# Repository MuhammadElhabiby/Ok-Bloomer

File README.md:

# Ok Bloomer

# How to Docker Windows
1. Docker Desktop runterladen und installieren https://docs.docker.com/desktop/install/windows-install/
2. WSL installieren
    1. Powershell als Admin ausführen
    2. wsl --install ausführen
    3. https://wslstorestorage.blob.core.windows.net/wslblob/wsl_update_x64.msi runterladen und installieren oder über Windows-Update installieren
4. PC neustarten
5. Docker Desktop starten und warten bis Docker Engine gestartet ist (unten links zu sehen, siehe Screenshot)

6. Konsole im repo öffnen
7. docker compose up --build ausführen
8. Nun werden die Docker Container gebaut und ausgeführt. Nach Änderungen muss der Befehl docker compose up --build erneut ausgeführt werden, um die Änderungen zu übernehmen

Die Docker Instanz kann ebenfalls über Docker Desktop verwaltet werden.

Ports:
- 127.0.0.1:7000 - Dashboard
- 127.0.0.1:7001 - MongoDB
- 127.0.0.1:7002 - MongoDB Admin Panel
- 127.0.0.1:7003 - MQTT Broker

MQTT Debug GUI Tool - https://github.com/thomasnordquist/MQTT-Explorer
https://github.com/thomasnordquist/MQTT-Explorer/releases/tag/v0.3.5

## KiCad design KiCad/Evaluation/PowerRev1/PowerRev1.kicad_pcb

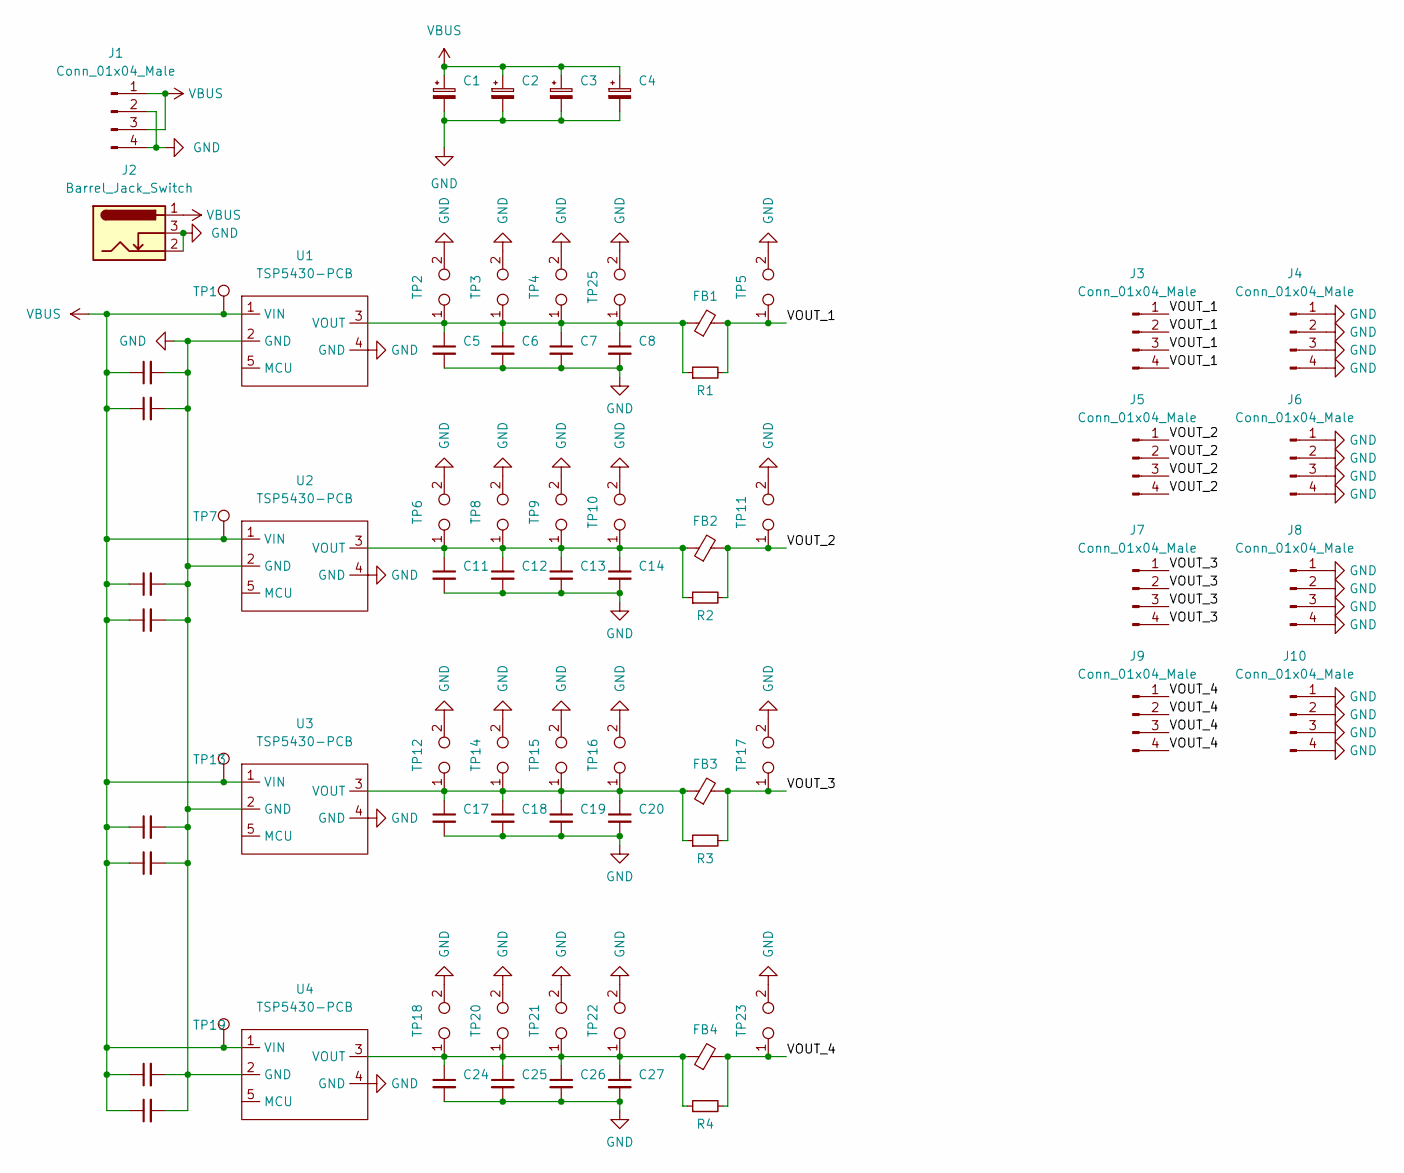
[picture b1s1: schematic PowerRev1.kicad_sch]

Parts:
C1, C2, C3, C4: C_Polarized_Small; CP_Radial_D8.0mm_P3.50mm
C5, C6, C7, C8, C9, C10, C11, C12, C13, C14, C15, C16, C17, C18, C19, C20, C21, C22, C23, C24, C25, C26, C27, C28: C_Small; 0805-1206Capacitor
FB1, FB2, FB3, FB4: FerriteBead_Small; 0805-1206Capacitor
J1, J3, J4, J5, J6, J7, J8, J9, J10: Conn_01x04_Male; PinSocket_1x04_P2.54mm_Vertical
J2: Barrel_Jack_Switch; BarrelJack_GCT_DCJ200-10-A_Horizontal
R1, R2, R3, R4: R_Small; 0805-1206Capacitor
TP1, TP7, TP13, TP19: TestPoint; TestPoint_Pad_D2.0mm
TP2, TP3, TP4, TP5, TP6, TP8, TP9, TP10, TP11, TP12, TP14, TP15, TP16, TP17, TP18, TP20, TP21, TP22, TP23, TP25: TestPoint_2Pole; TestPoint_2Pads_Pitch5.08mm_Drill1.3mm
U1, U2, U3, U4: TSP5430-PCB; TPS5430-REV3

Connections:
/VOUT_1: FB1.2, J3.1, J3.2, J3.3, J3.4, R1.2, TP5.1
/VOUT_2: FB2.2, J5.1, J5.2, J5.3, J5.4, R2.2, TP11.1
/VOUT_3: FB3.2, J7.1, J7.2, J7.3, J7.4, R3.2, TP17.1
/VOUT_4: FB4.2, J9.1, J9.2, J9.3, J9.4, R4.2, TP23.1
GND: C1.2, C2.2, C3.2, C4.2, C5.2, C6.2, C7.2, C8.2, C9.2, C10.2, C11.2, C12.2, C13.2, C14.2, C15.2, C16.2, C17.2, C18.2, C19.2, C20.2, C21.2, C22.2, C23.2, C24.2, C25.2, C26.2, C27.2, C28.2, J1.2, J1.4, J2.2, J2.3, J4.1, J4.2, J4.3, J4.4, J6.1, J6.2, J6.3, J6.4, J8.1, J8.2, J8.3, J8.4, J10.1, J10.2, J10.3, J10.4, TP2.2, TP3.2, TP4.2, TP5.2, TP6.2, TP8.2, TP9.2, TP10.2, TP11.2, TP12.2, TP14.2, TP15.2, TP16.2, TP17.2, TP18.2, TP20.2, TP21.2, TP22.2, TP23.2, TP25.2, U1.2 (GND), U1.4 (GND), U2.2 (GND), U2.4 (GND), U3.2 (GND), U3.4 (GND), U4.2 (GND), U4.4 (GND)
unnamed: C5.1, C6.1, C7.1, C8.1, FB1.1, R1.1, TP2.1, TP3.1, TP4.1, TP25.1, U1.3 (VOUT)
unnamed: C11.1, C12.1, C13.1, C14.1, FB2.1, R2.1, TP6.1, TP8.1, TP9.1, TP10.1, U2.3 (VOUT)
unnamed: C17.1, C18.1, C19.1, C20.1, FB3.1, R3.1, TP12.1, TP14.1, TP15.1, TP16.1, U3.3 (VOUT)
unnamed: C24.1, C25.1, C26.1, C27.1, FB4.1, R4.1, TP18.1, TP20.1, TP21.1, TP22.1, U4.3 (VOUT)
VBUS: C1.1, C2.1, C3.1, C4.1, C9.1, C10.1, C15.1, C16.1, C21.1, C22.1, C23.1, C28.1, J1.1, J1.3, J2.1, TP1.1, TP7.1, TP13.1, TP19.1, U1.1 (VIN), U2.1 (VIN), U3.1 (VIN), U4.1 (VIN)

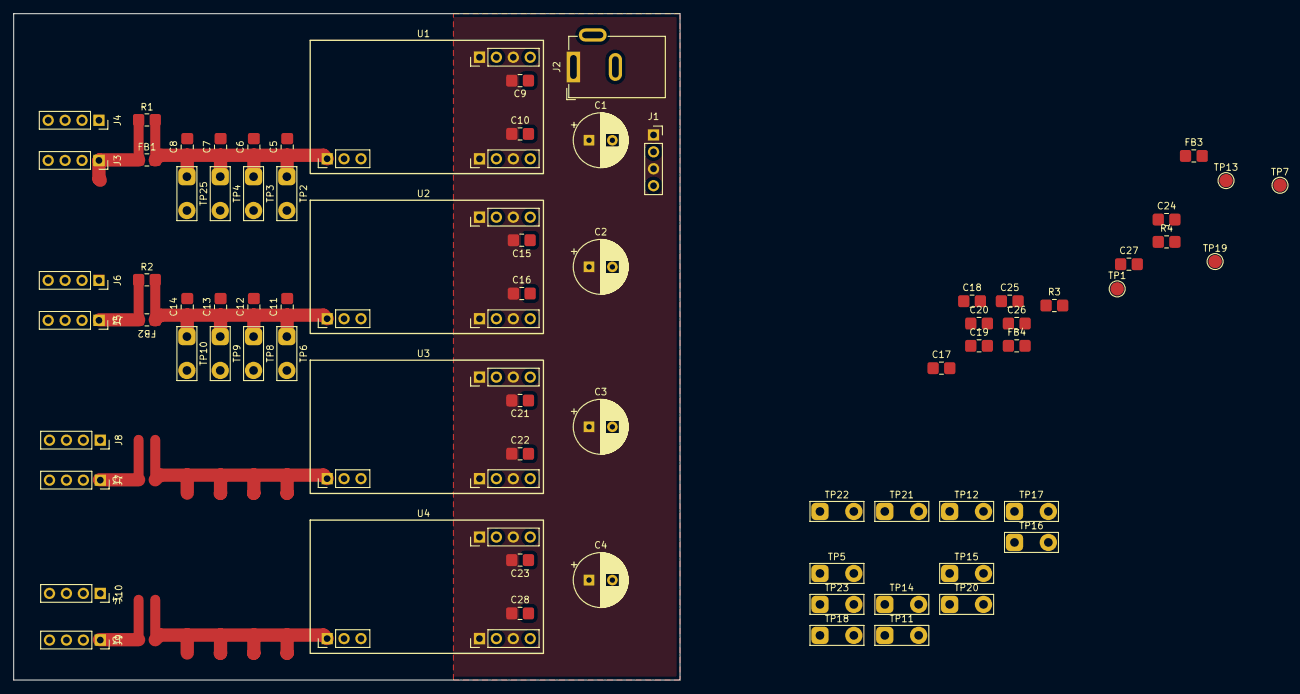
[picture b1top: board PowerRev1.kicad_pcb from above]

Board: 4 copper layers, 100.0 x 100.0 mm, 74 parts (0 on the bottom side), 10 nets.

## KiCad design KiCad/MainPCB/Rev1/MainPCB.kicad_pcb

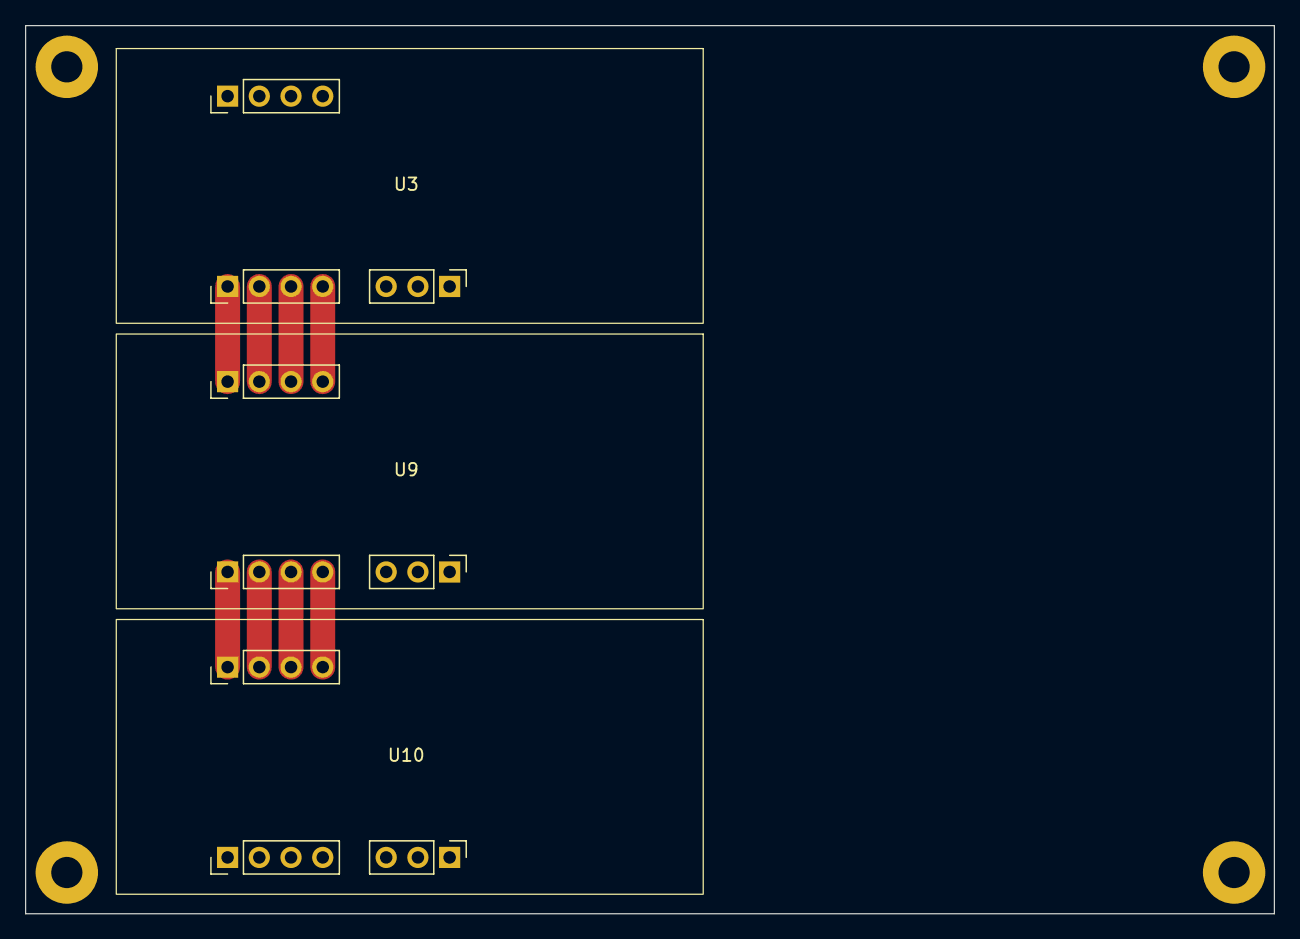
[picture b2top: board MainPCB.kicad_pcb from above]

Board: 2 copper layers, 100.0 x 71.1 mm, 7 parts (0 on the bottom side), 5 nets.

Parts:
H1, H2, H3, H4: MountingHole; MountingHole_2.5mm_Pad
U3, U9, U10: AOZ1016-PCB

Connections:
/MCU: U3.7 (MCU), U10.7 (MCU)
unnamed: U3.5 (GND), U9.3 (GND)
unnamed: U3.6 (VIN), U9.4 (VIN)
unnamed: U9.5 (GND), U10.3 (GND)
unnamed: U9.6 (VIN), U10.4 (VIN)

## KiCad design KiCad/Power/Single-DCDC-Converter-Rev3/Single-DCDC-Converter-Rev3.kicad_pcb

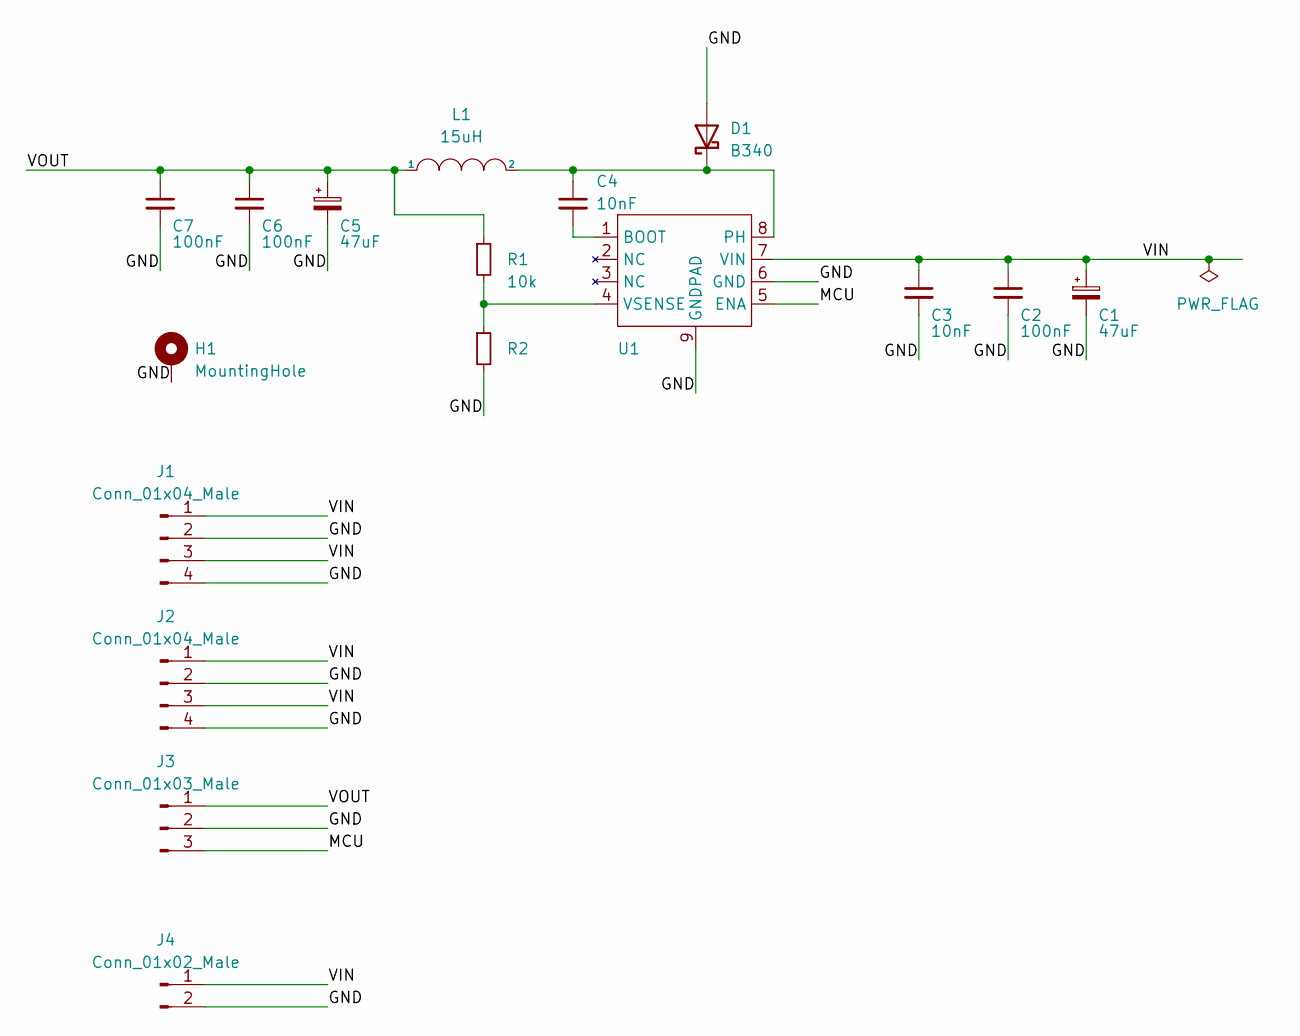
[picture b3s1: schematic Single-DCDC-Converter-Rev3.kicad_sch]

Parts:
C1, C5: 47uF; CP_Elec_6.3x5.9
C2: 100nF; C_0805_2012Metric
C3, C4: 10nF; C_0805_2012Metric
C6, C7: 100nF; 0805-1206Capacitor
D1: B340; D_SMA
H1: MountingHole; MountingHole_2.5mm_Pad
J1, J2: Conn_01x04_Male; PinHeader_1x04_P2.54mm_Vertical
J3: Conn_01x03_Male; PinHeader_1x03_P2.54mm_Vertical
J4: Conn_01x02_Male; PinSocket_1x02_P2.54mm_Vertical
L1: 15uH; PowerInductor-Murata-DEM8045Z-8x8
R1: 10k; R_0805_2012Metric
R2: R_Small; R_0805_2012Metric
U1: TPS5430; Texas_HSOP-8-1EP_3.9x4.9mm_P1.27mm_ThermalVias

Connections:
/GND: C1.2, C2.2, C3.2, C5.2, C6.2, C7.2, D1.2 (A), H1.1, J1.2, J1.4, J2.2, J2.4, J3.2, J4.2, R2.2, U1.6 (GND), U1.9 (GNDPAD)
/MCU: J3.3, U1.5 (ENA)
/VIN: C1.1, C2.1, C3.1, J1.1, J1.3, J2.1, J2.3, J4.1, U1.7 (VIN)
/VOUT: C5.1, C6.1, C7.1, J3.1, L1.1, R1.1
unnamed: C4.1, D1.1 (K), L1.2, U1.8 (PH)
unnamed: C4.2, U1.1 (BOOT)
unnamed: R1.2, R2.1, U1.4 (VSENSE)

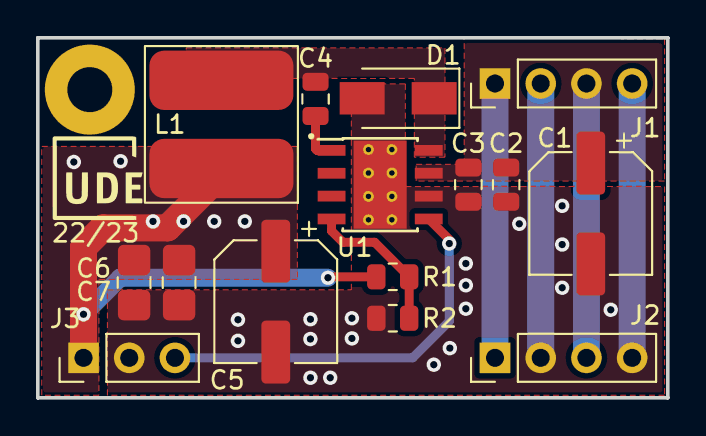
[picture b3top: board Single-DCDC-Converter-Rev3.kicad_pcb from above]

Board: 6 copper layers, 35.0 x 20.0 mm, 16 parts (0 on the bottom side), 7 nets.

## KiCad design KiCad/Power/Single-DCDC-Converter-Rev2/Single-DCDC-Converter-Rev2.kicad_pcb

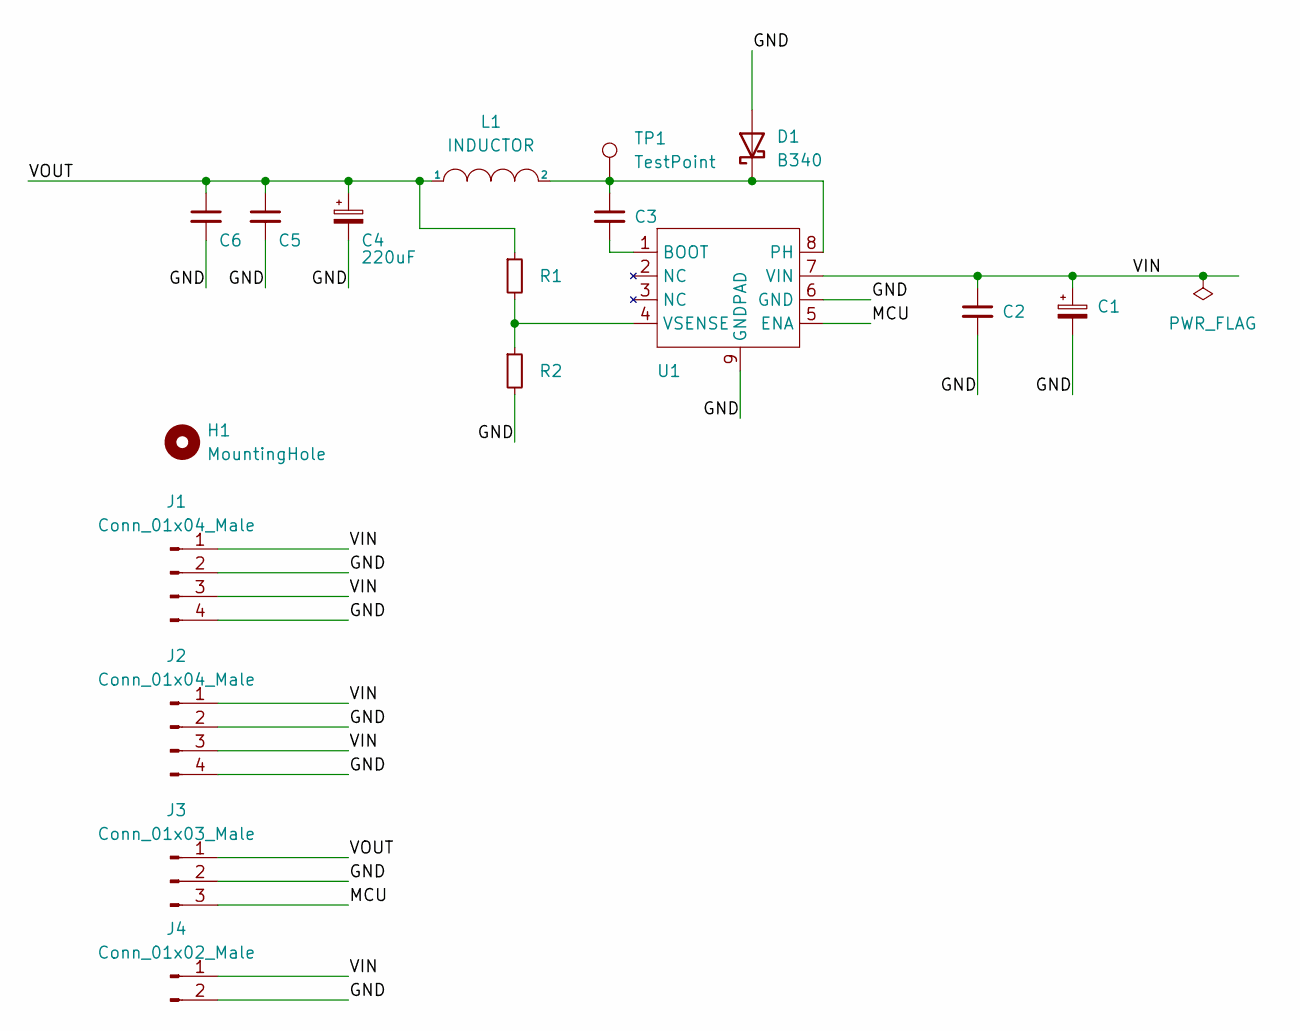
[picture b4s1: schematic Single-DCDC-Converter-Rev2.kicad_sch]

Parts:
C1: C_Polarized_Small; CP_Elec_10x10.5
C2, C3, C6: C_Small; C_0805_2012Metric_Pad1.18x1.45mm_HandSolder
C4: 220uF; CP_Elec_10x10.5
C5: C_Small; CP_Radial_D8.0mm_P3.50mm
D1: B340; D_SMA
H1: MountingHole; MountingHole_2.5mm_Pad
J1, J2: Conn_01x04_Male; PinHeader_1x04_P2.54mm_Vertical
J3: Conn_01x03_Male; PinHeader_1x03_P2.54mm_Vertical
J4: Conn_01x02_Male; PinSocket_1x02_P2.54mm_Vertical
L1: INDUCTOR; PowerInductor_Panasonic_ETQP3MKVN_7.4mm_7mm
R1, R2: R_Small; R_0805_2012Metric_Pad1.20x1.40mm_HandSolder
TP1: TestPoint; TestPoint_Pad_1.0x1.0mm
U1: TPS5430; Texas_HSOP-8-1EP_3.9x4.9mm_P1.27mm_ThermalVias

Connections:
/GND: C1.2, C2.2, C4.2, C5.2, C6.2, D1.2 (A), H1.1, J1.2, J1.4, J2.2, J2.4, J3.2, J4.2, R2.2, U1.6 (GND), U1.9 (GNDPAD)
/MCU: J3.3, U1.5 (ENA)
/VIN: C1.1, C2.1, J1.1, J1.3, J2.1, J2.3, J4.1, U1.7 (VIN)
/VOUT: C4.1, C5.1, C6.1, J3.1, L1.1, R1.1
unnamed: C3.1, D1.1 (K), L1.2, TP1.1, U1.8 (PH)
unnamed: C3.2, U1.1 (BOOT)
unnamed: R1.2, R2.1, U1.4 (VSENSE)

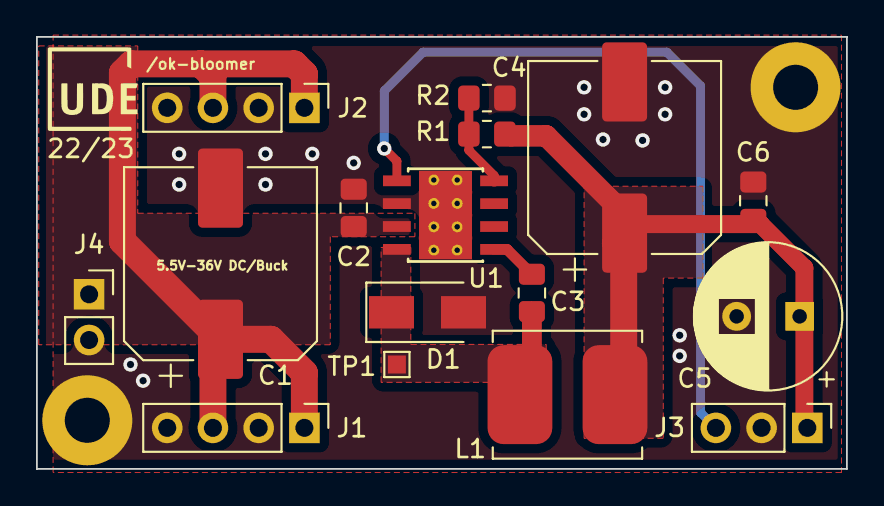
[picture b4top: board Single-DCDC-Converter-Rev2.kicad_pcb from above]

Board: 6 copper layers, 45.0 x 24.0 mm, 17 parts (0 on the bottom side), 7 nets.

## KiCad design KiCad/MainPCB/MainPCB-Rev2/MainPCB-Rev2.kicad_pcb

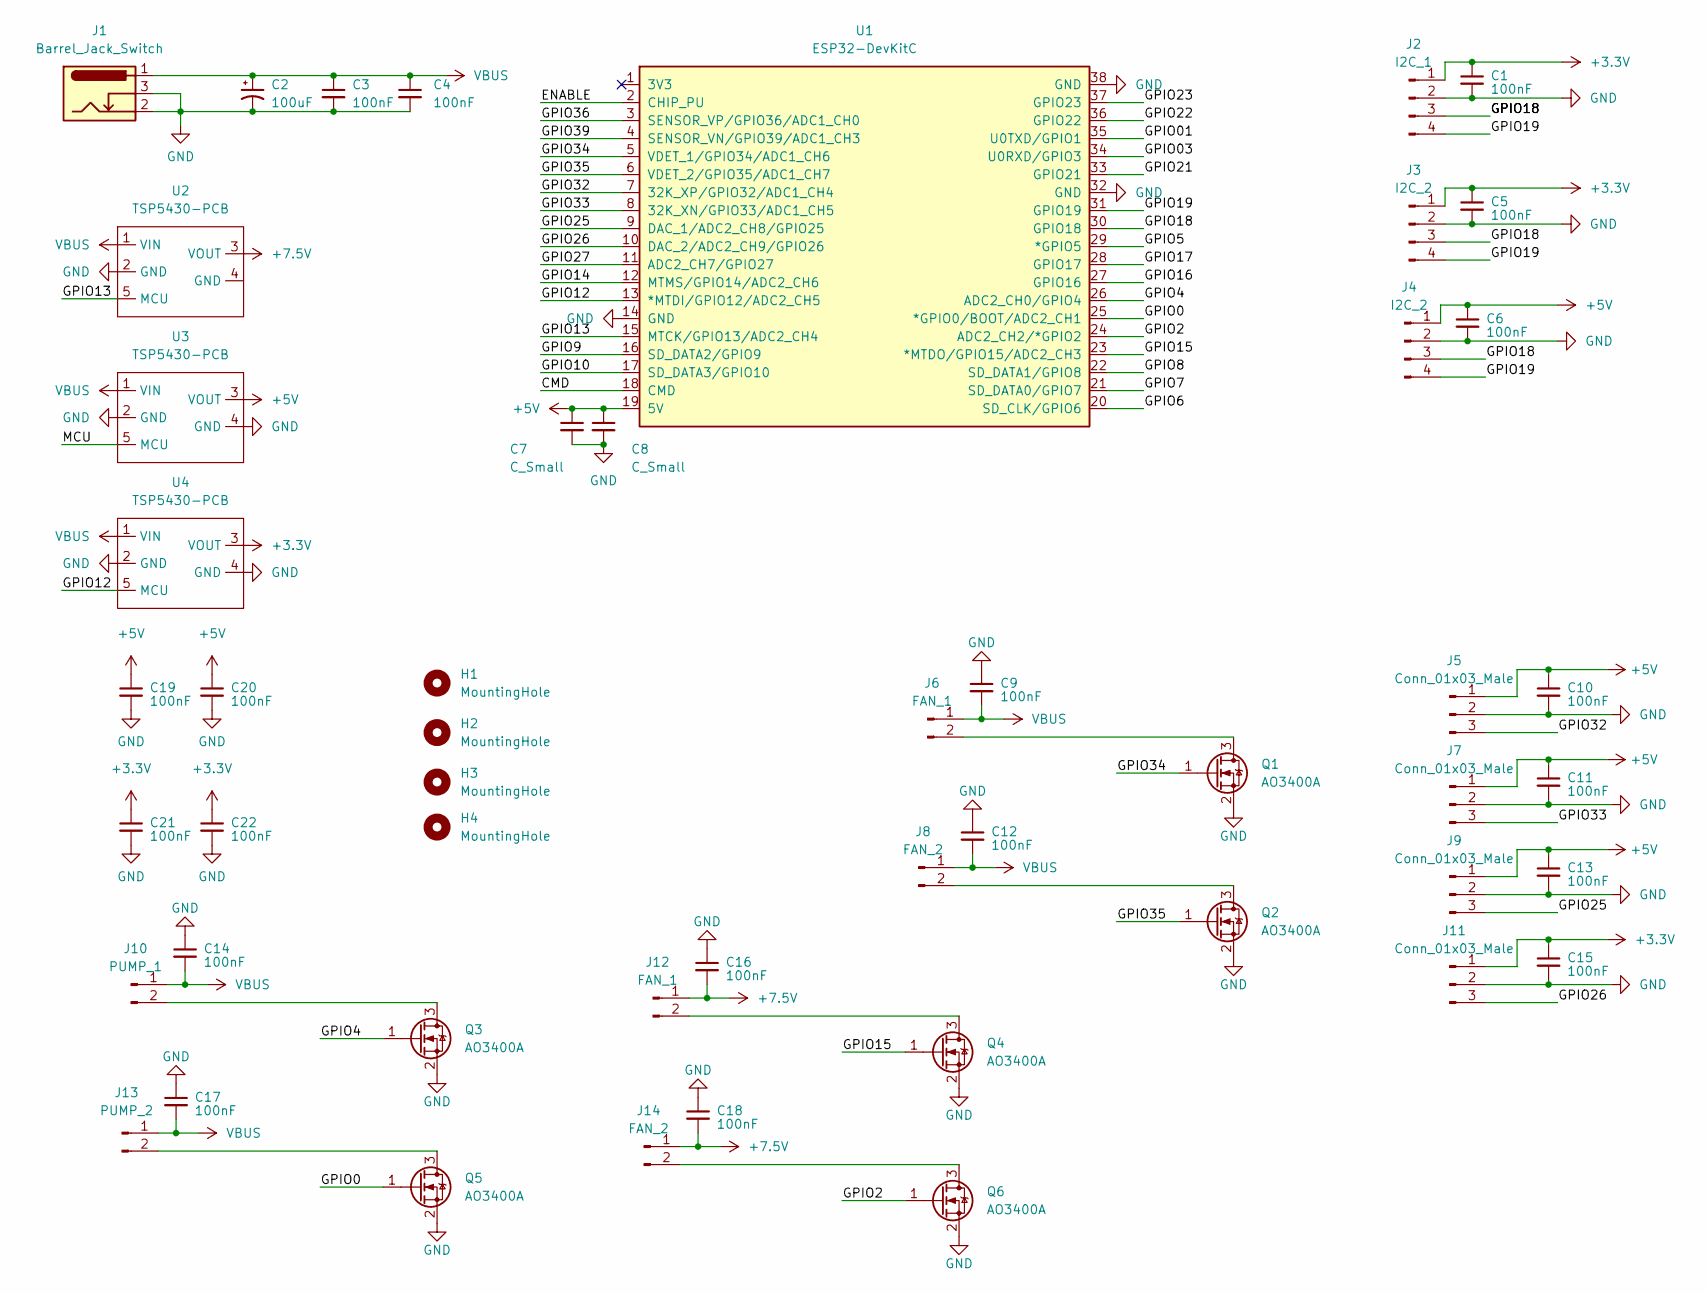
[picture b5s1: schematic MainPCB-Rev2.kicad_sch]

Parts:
C1, C3, C4, C5, C6, C9, C10, C11, C12, C13, C14, C15, C16, C17, C18, C19, C20, C21, C22: 100nF; 0805-1206Capacitor
C2: 100uF; CP_Radial_D8.0mm_P3.50mm
C7, C8: C_Small; 0805-1206Capacitor
H1, H2, H3, H4: MountingHole; MountingHole_2.5mm_Pad
J1: Barrel_Jack_Switch; BarrelJack_GCT_DCJ200-10-A_Horizontal
J2: I2C_1; JST_XH_B4B-XH-A_1x04_P2.50mm_Vertical
J3, J4: I2C_2; JST_XH_B4B-XH-A_1x04_P2.50mm_Vertical
J5, J7, J9, J11: Conn_01x03_Male; JST_XH_B3B-XH-A_1x03_P2.50mm_Vertical
J6, J12: FAN_1; JST_XH_B2B-XH-A_1x02_P2.50mm_Vertical
J8, J14: FAN_2; JST_XH_B2B-XH-A_1x02_P2.50mm_Vertical
J10: PUMP_1; JST_XH_B2B-XH-A_1x02_P2.50mm_Vertical
J13: PUMP_2; JST_XH_B2B-XH-A_1x02_P2.50mm_Vertical
Q1, Q2, Q3, Q4, Q5, Q6: AO3400A; SOT-23
U1: ESP32-DevKitC
U2, U3, U4: TSP5430-PCB; TPS5430-REV3

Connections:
+3.3V: C1.1, C5.1, C15.1, C21.1, C22.1, J2.1, J3.1, J11.1, U4.3 (VOUT)
+5V: C6.1, C7.1, C8.1, C10.1, C11.1, C13.1, C19.1, C20.1, J4.1, J5.1, J7.1, J9.1, U1.19 (5V), U3.3 (VOUT)
+7.5V: C16.2, C18.2, J12.1, J14.1, U2.3 (VOUT)
/CMD: U1.18 (CMD)
/ENABLE: U1.2 (CHIP_PU)
/GPIO0: Q5.1 (G), U1.25 (*GPIO0/BOOT/ADC2_CH1)
/GPIO01: U1.35 (U0TXD/GPIO1)
/GPIO2: Q6.1 (G), U1.24 (ADC2_CH2/*GPIO2)
/GPIO03: U1.34 (U0RXD/GPIO3)
/GPIO4: Q3.1 (G), U1.26 (ADC2_CH0/GPIO4)
/GPIO5: U1.29 (*GPIO5)
/GPIO6: U1.20 (SD_CLK/GPIO6)
/GPIO7: U1.21 (SD_DATA0/GPIO7)
/GPIO8: U1.22 (SD_DATA1/GPIO8)
/GPIO9: U1.16 (SD_DATA2/GPIO9)
/GPIO10: U1.17 (SD_DATA3/GPIO10)
/GPIO12: U1.13 (*MTDI/GPIO12/ADC2_CH5), U4.5 (MCU)
/GPIO13: U1.15 (MTCK/GPIO13/ADC2_CH4), U2.5 (MCU)
/GPIO14: U1.12 (MTMS/GPIO14/ADC2_CH6)
/GPIO15: Q4.1 (G), U1.23 (*MTDO/GPIO15/ADC2_CH3)
/GPIO16: U1.27 (GPIO16)
/GPIO17: U1.28 (GPIO17)
/GPIO18: J2.3, J3.3, J4.3, U1.30 (GPIO18)
/GPIO19: J2.4, J3.4, J4.4, U1.31 (GPIO19)
/GPIO21: U1.33 (GPIO21)
/GPIO22: U1.36 (GPIO22)
/GPIO23: U1.37 (GPIO23)
/GPIO25: J9.3, U1.9 (DAC_1/ADC2_CH8/GPIO25)
/GPIO26: J11.3, U1.10 (DAC_2/ADC2_CH9/GPIO26)
/GPIO27: U1.11 (ADC2_CH7/GPIO27)
/GPIO32: J5.3, U1.7 (32K_XP/GPIO32/ADC1_CH4)
/GPIO33: J7.3, U1.8 (32K_XN/GPIO33/ADC1_CH5)
/GPIO34: Q1.1 (G), U1.5 (VDET_1/GPIO34/ADC1_CH6)
/GPIO35: Q2.1 (G), U1.6 (VDET_2/GPIO35/ADC1_CH7)
/GPIO36: U1.3 (SENSOR_VP/GPIO36/ADC1_CH0)
/GPIO39: U1.4 (SENSOR_VN/GPIO39/ADC1_CH3)
/MCU: U3.5 (MCU)
GND: C1.2, C2.2, C3.2, C4.2, C5.2, C6.2, C7.2, C8.2, C9.1, C10.2, C11.2, C12.1, C13.2, C14.1, C15.2, C16.1, C17.1, C18.1, C19.2, C20.2, C21.2, C22.2, J1.2, J1.3, J2.2, J3.2, J4.2, J5.2, J7.2, J9.2, J11.2, Q1.2 (S), Q2.2 (S), Q3.2 (S), Q4.2 (S), Q5.2 (S), Q6.2 (S), U1.14 (GND), U1.32 (GND), U1.38 (GND), U2.2 (GND), U3.2 (GND), U3.4 (GND), U4.2 (GND), U4.4 (GND)
unnamed: J6.2, Q1.3 (D)
unnamed: J8.2, Q2.3 (D)
unnamed: J10.2, Q3.3 (D)
unnamed: J12.2, Q4.3 (D)
unnamed: J13.2, Q5.3 (D)
unnamed: J14.2, Q6.3 (D)
VBUS: C2.1, C3.1, C4.1, C9.2, C12.2, C14.2, C17.2, J1.1, J6.1, J8.1, J10.1, J13.1, U2.1 (VIN), U3.1 (VIN), U4.1 (VIN)

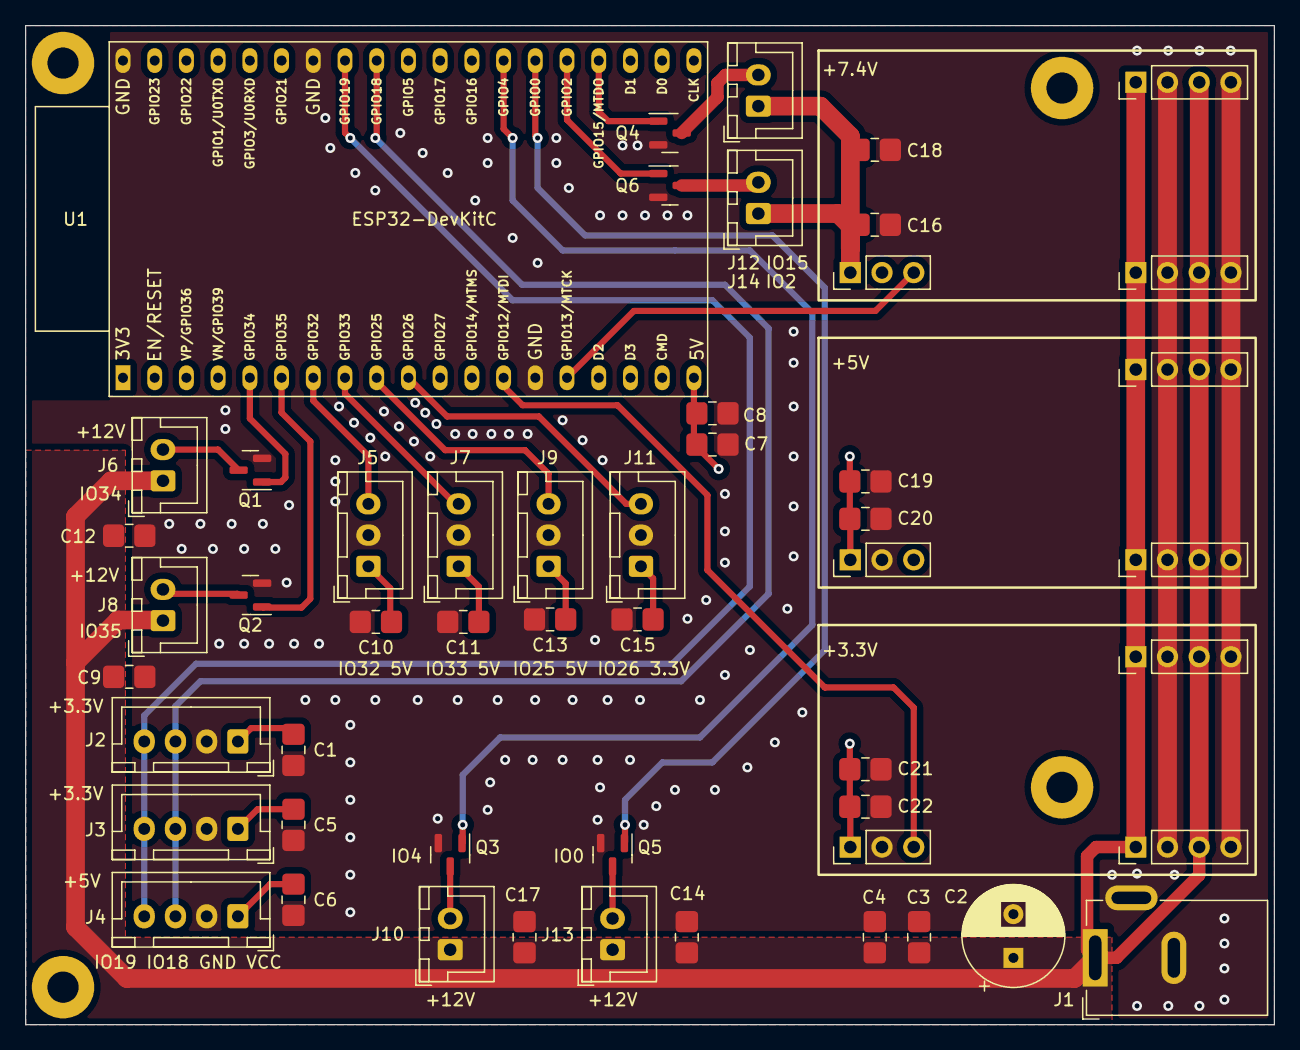
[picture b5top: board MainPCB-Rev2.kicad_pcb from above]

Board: 4 copper layers, 100.0 x 80.0 mm, 51 parts (1 on the bottom side), 25 nets.

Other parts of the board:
Ge: LOGO

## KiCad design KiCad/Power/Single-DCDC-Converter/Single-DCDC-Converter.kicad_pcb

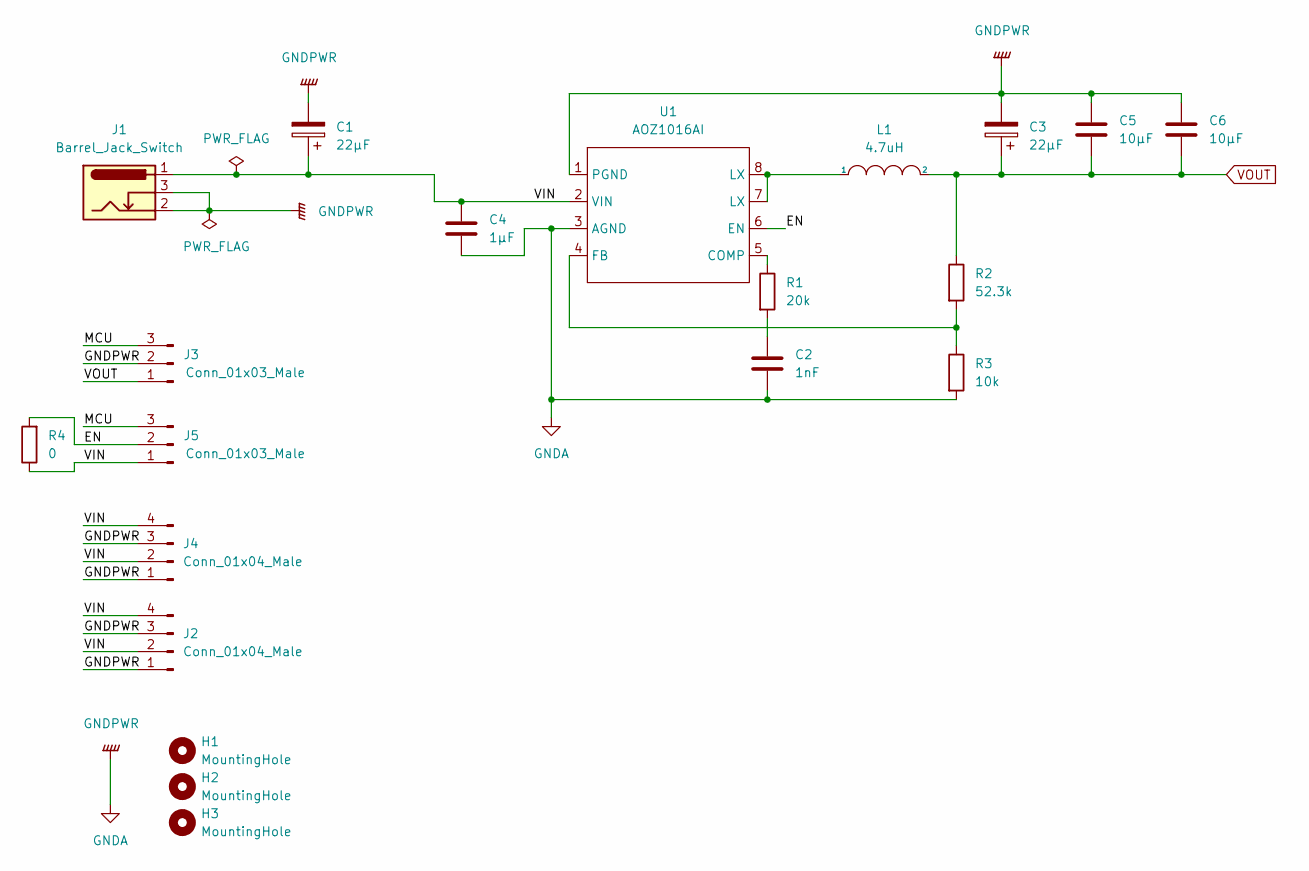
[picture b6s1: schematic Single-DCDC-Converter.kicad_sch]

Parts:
C1, C3: 22µF; CP_Elec_6.3x5.9
C2: 1nF; C_0805_2012Metric_Pad1.18x1.45mm_HandSolder
C4: 1µF; C_0805_2012Metric_Pad1.18x1.45mm_HandSolder
C5, C6: 10µF; C_0805_2012Metric_Pad1.18x1.45mm_HandSolder
H1, H2, H3: MountingHole; MountingHole_2.5mm_Pad
J1: Barrel_Jack_Switch; BarrelJack_GCT_DCJ200-10-A_Horizontal
J2, J4: Conn_01x04_Male; PinHeader_1x04_P2.54mm_Vertical
J3, J5: Conn_01x03_Male; PinHeader_1x03_P2.54mm_Vertical
L1: 4.7uH; PowerInductor_Panasonic_ETQP3MKVN_7.4mm_7mm
R1: 20k; R_0805_2012Metric_Pad1.20x1.40mm_HandSolder
R2: 52.3k; R_0805_2012Metric_Pad1.20x1.40mm_HandSolder
R3: 10k; R_0805_2012Metric_Pad1.20x1.40mm_HandSolder
R4: 0; R_0402_1005Metric
U1: AOZ1016AI; SO-8_3.9x4.9mm_P1.27mm

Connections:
/EN: J5.2, R4.2, U1.6 (EN)
/MCU: J3.3, J5.3
/VIN: C1.1, C4.2, J1.1, J2.2, J2.4, J4.2, J4.4, J5.1, R4.1, U1.2 (VIN)
GNDA: C1.2, C2.2, C3.2, C4.1, C5.1, C6.1, J1.2, J1.3, J2.1, J2.3, J3.2, J4.1, J4.3, R3.2, U1.1 (PGND), U1.3 (AGND)
unnamed: C2.1, R1.2
unnamed: L1.1, U1.7 (LX), U1.8 (LX)
unnamed: R1.1, U1.5 (COMP)
unnamed: R2.2, R3.1, U1.4 (FB)
VOUT: C3.1, C5.2, C6.2, J3.1, L1.2, R2.1

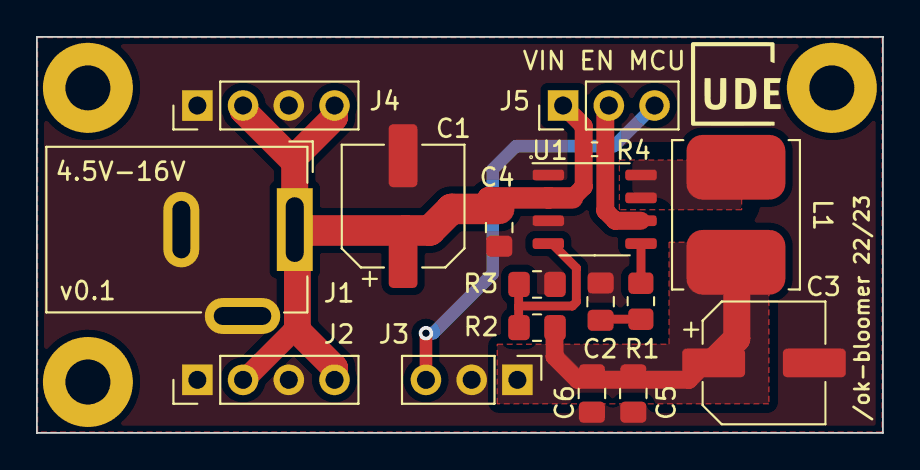
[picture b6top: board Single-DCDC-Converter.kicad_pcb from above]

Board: 2 copper layers, 47.0 x 22.0 mm, 20 parts (0 on the bottom side), 9 nets.

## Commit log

2024-09-03 Ok-Bloomer
